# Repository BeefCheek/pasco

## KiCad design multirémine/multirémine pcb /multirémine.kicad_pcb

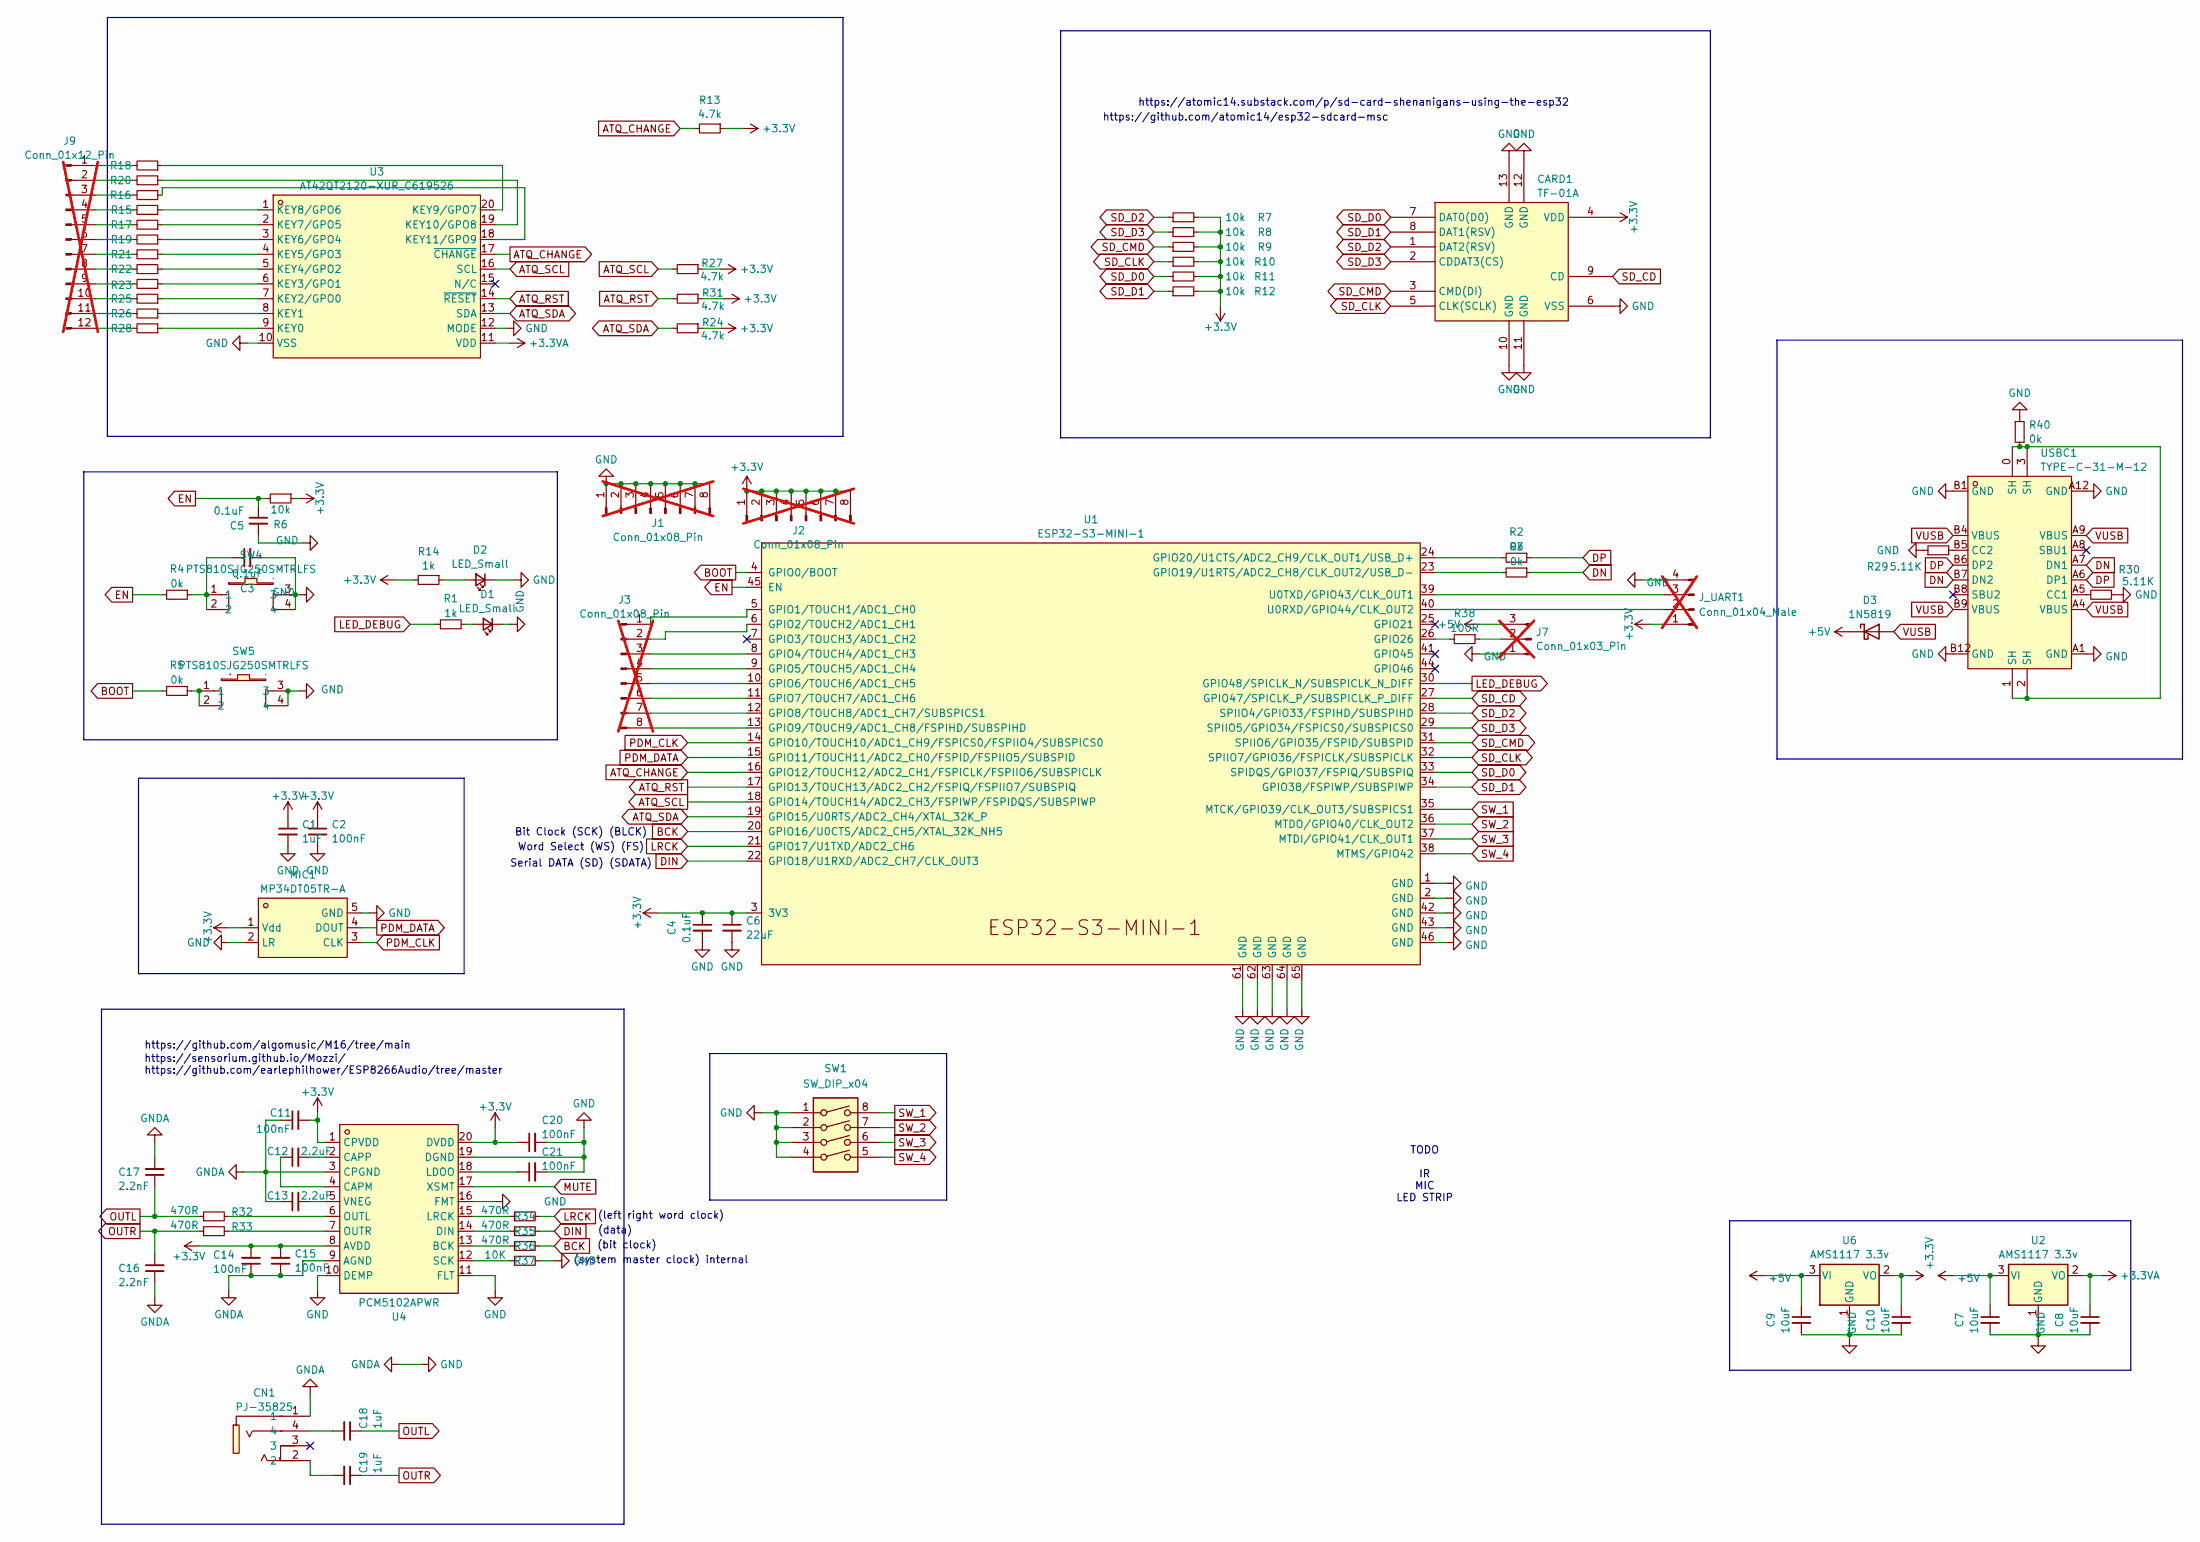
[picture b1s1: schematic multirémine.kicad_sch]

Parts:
C1, C18, C19: 1uF; C_0805_2012Metric
C2, C11, C14, C15, C20, C21: 100nF; C_0805_2012Metric
C3, C4, C5: 0.1uF; C_0805_2012Metric
C6: 22uF; C_0805_2012Metric
C7, C8, C9, C10: 10uF; C_0805_2012Metric
C12, C13: 2.2uF; C_0805_2012Metric
C16, C17: 2.2nF; C_0805_2012Metric
CARD1: TF-01A; TF-SMD_TF-01A; LCSC Part C91145
CN1: PJ-35825; AUDIO-SMD_PJ-35825; LCSC Part C2764616
D1, D2: LED_Small; LED_0805_2012Metric
D3: 1N5819; D_SOD-123
J1, J2, J3: Conn_01x08_Pin; PinHeader_1x08_P2.54mm_Vertical; not fitted
J7: Conn_01x03_Pin; PinHeader_1x03_P2.54mm_Vertical; not fitted
J9: Conn_01x12_Pin; TerminalBlock_4Ucon_1x12_P3.50mm_Horizontal; not fitted
J_UART1: Conn_01x04_Male; PinHeader_1x04_P2.54mm_Vertical; not fitted
MIC1: MP34DT05TR-A; MIC-SMD_5P-L3.0-W4.0-P0.85-BL; LCSC Part C2688664
R1: 1k; R_0805_2012Metric
R2, R3, R4, R5, R40: 0k; R_0805_2012Metric
R6, R7, R8, R9, R10, R11, R12: 10k; R_0805_2012Metric
R13, R24, R27, R31: 4.7k; R_0805_2012Metric_Pad1.20x1.40mm_HandSolder
R14: 1k; R_0805_2012Metric_Pad1.20x1.40mm_HandSolder
R15, R16, R17, R18, R19, R20, R21, R22, R23, R25, R26, R28: 20k; R_0805_2012Metric_Pad1.20x1.40mm_HandSolder
R29, R30: 5.11K; R_0805_2012Metric
R32, R33, R34, R35, R36: 470R; R_0805_2012Metric
R37: 10K; R_0805_2012Metric
R38: 100R; R_0805_2012Metric
SW1: SW_DIP_x04; SW-SMD_EM-04KP; MPN C129080
SW4, SW5: PTS810SJG250SMTRLFS; SW-SMD_4P_PTS810SJM250SMTRLFS; LCSC Part C221895
U1: ESP32-S3-MINI-1; MPN C2913206
U2, U6: AMS1117 3.3v; SOT-223-3_TabPin2
U3: AT42QT2120-XUR_C619526; TSSOP-20_L6.5-W4.4-P0.65-LS6.4-TL; LCSC Part C619526
U4: PCM5102APWR; TSSOP-20_L6.5-W4.4-P0.65-LS6.4-BL; LCSC Part C107671
USBC1: TYPE-C-31-M-12; USB-C_SMD-TYPE-C-31-M-12; MPN C165948; LCSC Part C165948

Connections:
+3.3V: C1.1, C2.1, C4.1, C6.1, C10.1, C11.2, C14.2, C15.2, C20.1, CARD1.4 (VDD), J2.1, J2.2, J2.3, J2.4, J2.5, J2.6, J2.7, J2.8, J_UART1.1, MIC1.1 (Vdd), R6.1, R7.2, R8.2, R9.2, R10.2, R11.2, R12.2, R13.1, R14.2, R24.1, R27.1, R31.1, U1.3 (3V3), U4.1 (CPVDD), U4.8 (AVDD), U4.20 (DVDD), U6.2 (VO)
+3.3VA: C8.1, U2.2 (VO), U3.11 (VDD)
+5V: C7.1, C9.1, D3.1 (K), J7.3, U2.3 (VI), U6.3 (VI)
ATQ_CHANGE: R13.2, U1.16 (GPIO12/TOUCH12/ADC2_CH1/FSPICLK/FSPIIO6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), U3.17 (~CHANGE)
ATQ_RST: R31.2, U1.17 (GPIO13/TOUCH13/ADC2_CH2/FSPIQ/FSPIIO7/S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), U3.14 (~RESET)
ATQ_SCL: R27.2, U1.18 (GPIO14/TOUCH14/ADC2_CH3/FSPIWP/FSPIDQS/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), U3.16 (SCL)
ATQ_SDA: R24.2, U1.19 (GPIO15/U0RTS/ADC2_CH4/XTAL_32K_P), U3.13 (SDA)
BCK: R36.2, U1.20 (GPIO16/U0CTS/ADC2_CH5/XTAL_32K_NH5)
BOOT: R5.2, U1.4 (GPIO0/BOOT)
DIN: R35.2, U1.22 (GPIO18/U1RXD/ADC2_CH7/CLK_OUT3)
DN: R3.1, USBC1.A7 (DN1), USBC1.B7 (DN2)
DP: R2.1, USBC1.A6 (DP1), USBC1.B6 (DP2)
EN: C5.1, R4.2, R6.2, U1.45 (EN)
GND: C1.2, C2.2, C3.2, C4.2, C5.2, C6.2, C7.2, C8.2, C9.2, C10.2, C11.1, C13.1, C14.1, C15.1, C16.1, C17.2, C20.2, C21.2, CARD1.6 (VSS), CARD1.10 (GND), CARD1.11 (GND), CARD1.12 (GND), CARD1.13 (GND), CN1.1, D1.1 (K), D2.1 (K), J1.1, J1.2, J1.3, J1.4, J1.5, J1.6, J1.7, J1.8, J7.1, J_UART1.4, MIC1.2 (LR), MIC1.5 (GND), R29.1, R30.1, R37.2, R40.1, SW1.1, SW1.2, SW1.3, SW1.4, SW4.3, SW4.4, SW5.3, SW5.4, U1.1 (GND), U1.2 (GND), U1.42 (GND), U1.43 (GND), U1.46 (GND), U1.61 (GND), U1.62 (GND), U1.63 (GND), U1.64 (GND), U1.65 (GND), U2.1 (GND), U3.10 (VSS), U3.12 (MODE), U4.3 (CPGND), U4.9 (AGND), U4.10 (DEMP), U4.11 (FLT), U4.16 (FMT), U4.19 (DGND), U6.1 (GND), USBC1.A1 (GND), USBC1.A12 (GND), USBC1.B1 (GND), USBC1.B12 (GND)
LED_DEBUG: R1.1, U1.30 (GPIO48/SPICLK_N/SUBSPICLK_N_DIFF)
LRCK: R34.2, U1.21 (GPIO17/U1TXD/ADC2_CH6)
MUTE: U4.17 (XSMT)
unnamed: C3.1, R4.1, SW4.1, SW4.2
unnamed: C18.2, CN1.4
unnamed: C19.2, CN1.2
unnamed: D1.2 (A), R1.2
unnamed: D2.2 (A), R14.1
unnamed: J3.1, U1.5 (GPIO1/TOUCH1/ADC1_CH0)
unnamed: J3.2, U1.6 (GPIO2/TOUCH2/ADC1_CH1)
unnamed: J3.3, U1.8 (GPIO4/TOUCH4/ADC1_CH3)
unnamed: J3.4, U1.9 (GPIO5/TOUCH5/ADC1_CH4)
unnamed: J3.5, U1.10 (GPIO6/TOUCH6/ADC1_CH5)
unnamed: J3.6, U1.11 (GPIO7/TOUCH7/ADC1_CH6)
unnamed: J3.7, U1.12 (GPIO8/TOUCH8/ADC1_CH7/SUBSPICS1)
unnamed: J3.8, U1.13 (GPIO9/TOUCH9/ADC1_CH8/FSPIHD/SUBSPIHD)
unnamed: J7.2, R38.1
unnamed: J9.1, R18.2
unnamed: J9.2, R20.2
unnamed: J9.3, R16.2
unnamed: J9.4, R15.2
unnamed: J9.5, R17.2
unnamed: J9.6, R19.2
unnamed: J9.7, R21.2
unnamed: J9.8, R22.2
unnamed: J9.9, R23.2
unnamed: J9.10, R25.2
unnamed: J9.11, R26.2
unnamed: J9.12, R28.2
unnamed: J_UART1.2, U1.40 (U0RXD/GPIO44/CLK_OUT2)
unnamed: J_UART1.3, U1.39 (U0TXD/GPIO43/CLK_OUT1)
unnamed: R5.1, SW5.1, SW5.2
unnamed: R40.2, USBC1.0 (SH), USBC1.1 (SH), USBC1.2 (SH), USBC1.3 (SH)
unnamed: R3.2, U1.23 (GPIO19/U1RTS/ADC2_CH8/CLK_OUT2/USB_D-)
unnamed: R2.2, U1.24 (GPIO20/U1CTS/ADC2_CH9/CLK_OUT1/USB_D+)
unnamed: R38.2, U1.26 (GPIO26)
unnamed: R28.1, U3.9 (KEY0)
unnamed: R26.1, U3.8 (KEY1)
unnamed: R25.1, U3.7 (KEY2/GPO0)
unnamed: R23.1, U3.6 (KEY3/GPO1)
unnamed: R22.1, U3.5 (KEY4/GPO2)
unnamed: R21.1, U3.4 (KEY5/GPO3)
unnamed: R19.1, U3.3 (KEY6/GPO4)
unnamed: R17.1, U3.2 (KEY7/GPO5)
unnamed: R15.1, U3.1 (KEY8/GPO6)
unnamed: R18.1, U3.20 (KEY9/GPO7)
unnamed: R20.1, U3.19 (KEY10/GPO8)
unnamed: R16.1, U3.18 (KEY11/GPO9)
unnamed: R36.1, U4.13 (BCK)
unnamed: C12.1, U4.4 (CAPM)
unnamed: C12.2, U4.2 (CAPP)
unnamed: R35.1, U4.14 (DIN)
unnamed: C21.1, U4.18 (LDOO)
unnamed: R34.1, U4.15 (LRCK)
unnamed: R32.2, U4.6 (OUTL)
unnamed: R33.2, U4.7 (OUTR)
unnamed: R37.1, U4.12 (SCK)
unnamed: C13.2, U4.5 (VNEG)
unnamed: R30.2, USBC1.A5 (CC1)
unnamed: R29.2, USBC1.B5 (CC2)
OUTL: C17.1, C18.1, R32.1
OUTR: C16.2, C19.1, R33.1
PDM_CLK: MIC1.3 (CLK), U1.14 (GPIO10/TOUCH10/ADC1_CH9/FSPICS0/FSPIIO4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)
PDM_DATA: MIC1.4 (DOUT), U1.15 (GPIO11/TOUCH11/ADC2_CH0/FSPID/FSPIIO5/S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)
SD_CD: CARD1.9 (CD), U1.27 (GPIO47/SPICLK_P/SUBSPICLK_P_DIFF)
SD_CLK: CARD1.5 (CLK(SCLK)), R10.1, U1.32 (SPIIO7/GPIO36/FSPICLK/SUBSPICLK)
SD_CMD: CARD1.3 (CMD(DI)), R9.1, U1.31 (SPIIO6/GPIO35/FSPID/SUBSPID)
SD_D0: CARD1.7 (DAT0(D0)), R11.1, U1.33 (SPIDQS/GPIO37/FSPIQ/SUBSPIQ)
SD_D1: CARD1.8 (DAT1(RSV)), R12.1, U1.34 (GPIO38/FSPIWP/SUBSPIWP)
SD_D2: CARD1.1 (DAT2(RSV)), R7.1, U1.28 (SPIIO4/GPIO33/FSPIHD/SUBSPIHD)
SD_D3: CARD1.2 (CDDAT3(CS)), R8.1, U1.29 (SPIIO5/GPIO34/FSPICS0/SUBSPICS0)
SW_1: SW1.8, U1.35 (MTCK/GPIO39/CLK_OUT3/SUBSPICS1)
SW_2: SW1.7, U1.36 (MTDO/GPIO40/CLK_OUT2)
SW_3: SW1.6, U1.37 (MTDI/GPIO41/CLK_OUT1)
SW_4: SW1.5, U1.38 (MTMS/GPIO42)
VUSB: D3.2 (A), USBC1.A4 (VBUS), USBC1.A9 (VBUS), USBC1.B4 (VBUS), USBC1.B9 (VBUS)

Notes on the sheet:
Serial DATA (SD) (SDATA)
(bit clock)
TODO IR MIC LED STRIP
Word Select (WS) (FS)
https://github.com/algomusic/M16/tree/main
(system master clock) internal
(data)
https://atomic14.substack.com/p/sd-card-shenanigans-using-the-esp32
https://github.com/earlephilhower/ESP8266Audio/tree/master
https://github.com/atomic14/esp32-sdcard-msc
(left right word clock)
https://sensorium.github.io/Mozzi/
Bit Clock (SCK) (BLCK)

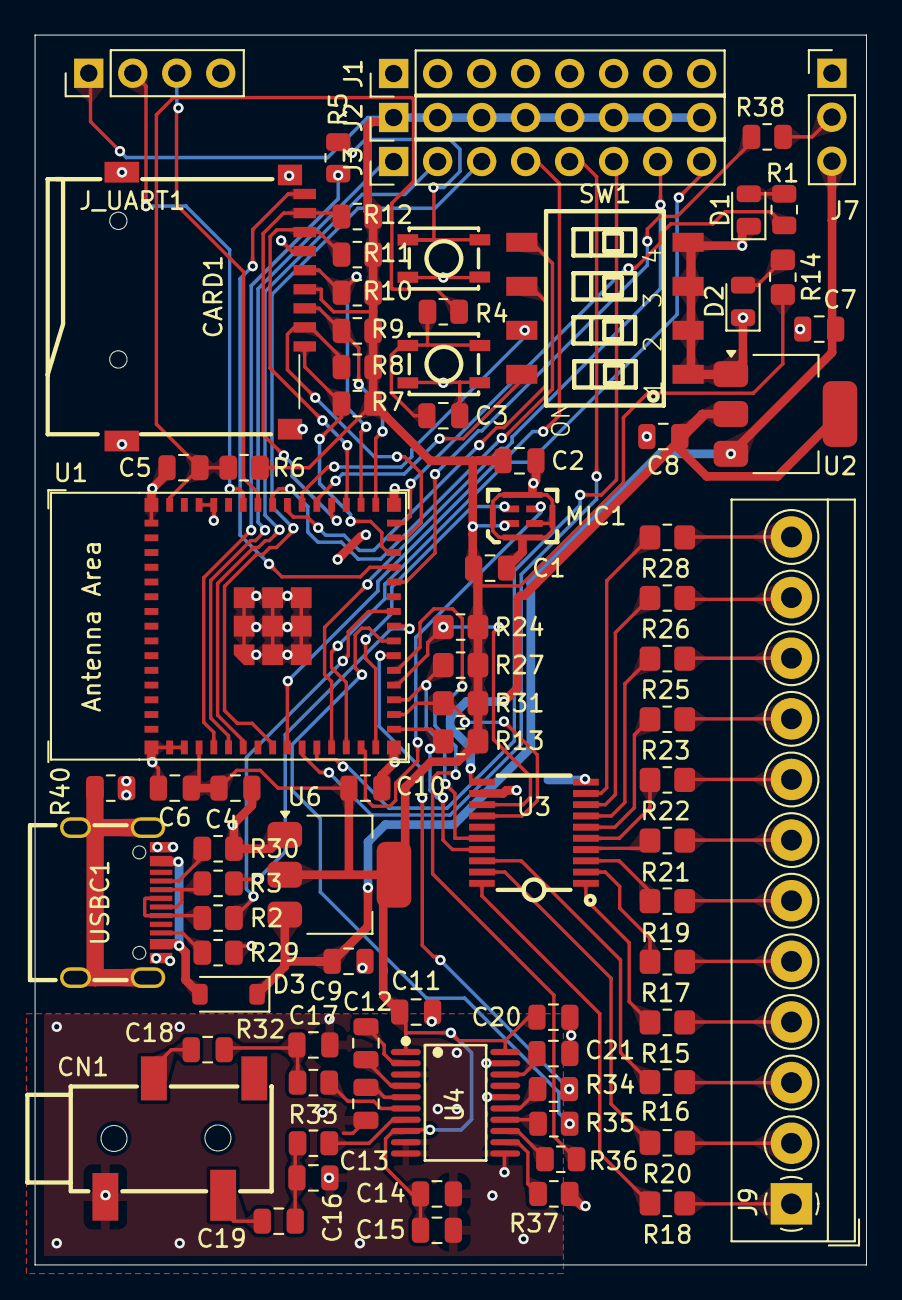
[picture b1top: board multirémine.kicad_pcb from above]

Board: 2 copper layers, 48.0 x 71.0 mm, 81 parts (0 on the bottom side), 89 nets.

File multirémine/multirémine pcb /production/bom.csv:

Designator,Footprint,Quantity,Value,LCSC Part #
"C1, C18, C19",0805,3,1uF,
"C10, C7, C8, C9",0805,4,10uF,
"C11, C14, C15, C2, C20, C21",0805,6,100nF,
"C12, C13",0805,2,2.2uF,
"C16, C17",0805,2,2.2nF,
"C3, C4, C5",0805,3,0.1uF,
C6,0805,1,22uF,
CARD1,TF-SMD_TF-01A,1,TF-01A,C91145
CN1,AUDIO-SMD_PJ-35825,1,PJ-35825,C2764616
"D1, D2",0805,2,LED_Small, C389524 
D3,D_SOD-123,1,1N5819,
MIC1,MIC-SMD_5P-L3.0-W4.0-P0.85-BL,1,MP34DT05TR-A,C2688664
R1,0805,1,1k,
"R10, R11, R12, R37, R6, R7, R8, R9",0805,8,10k,
"R13, R24, R27, R31",0805,4,4.7k,
R14,0805,1,1k,
"R15, R16, R17, R18, R19, R20, R21, R22, R23, R25, R26, R28",0805,12,20k,
"R2, R3, R4, R40, R5",0805,5,0k,
"R29, R30",0805,2,5.11K,
"R32, R33, R34, R35, R36",0805,5,470R,
R38,0805,1,100R,
SW1,SW-SMD_EM-04KP,1,SW_DIP_x04, C129080 
"SW4, SW5",SW-SMD_4P_PTS810SJM250SMTRLFS,2,PTS810SJG250SMTRLFS,C221895
U1,ESP32-S3-MINI-1,1,ESP32-S3-MINI-1,C2913206
"U2, U6",SOT-223-3_TabPin2,2,AMS1117 3.3v,
U3,TSSOP-20_L6.5-W4.4-P0.65-LS6.4-TL,1,AT42QT2120-XUR_C619526,C619526
U4,TSSOP-20_L6.5-W4.4-P0.65-LS6.4-BL,1,PCM5102APWR,C107671
USBC1,USB-C_SMD-TYPE-C-31-M-12,1,TYPE-C-31-M-12,C165948

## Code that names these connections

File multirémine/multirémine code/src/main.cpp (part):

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#define LED 48

// ATQ touch sensor
#define ATQ_CHANGE 12
#define ATQ_RST 13
#define ATQ_SDA 15
#define ATQ_SCL 14

volatile bool touchedDetected = false;

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void setupM16() {
  Osc::sinGen(waveTable); // fill the wavetable
  aOsc1.setPitch(69);
  seti2sPins(16, 17, 18, -1); // bck, ws, data_out, data_in // change ESP32 defaults
  audioStart();
}
void setupSensor() {
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void setup() {
  pinMode(LED, OUTPUT);

  pinMode(ATQ_RST, OUTPUT);
  digitalWrite(ATQ_RST, HIGH);

  Serial.begin(115200);
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
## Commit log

2025-08-08 altered changes
2025-10-01 working_patcher
2025-10-08 about stable
2025-10-08 make it sticky
2025-10-08 one plays one modulates
2025-10-08 smoothed out
2025-10-17 alt calib when in low range
2025-10-22 fixed an espressif32 version
2025-11-03 smoothesd kaplan
2025-11-03 new calib and foolproof buffers
2025-11-03 added motion cumulator
2025-11-03 Tuned stuck-touch handling: introduced motion accumulation and a recenter threshold so legitimate presses never rebaseline mid-touch, while sensors that latch without movement still auto-recover.
